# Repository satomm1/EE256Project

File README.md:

# EE 256 Project --- The Smart Pot
Matthew Sato <br />
satomm@stanford.edu <br />
Autumn 2023

This repository contains three folders: [`electrical`](electrical), [`software`](software), and [`docs`](docs) which contain all the project deliverables for this project. The project summary with my perspectives on this project is located at the [bottom of this page](#project-summary).

## The Smart Pot
The smart pot is designed as a completely autonomous plant pot that gives you the ability to be a plant parent without the trouble of remembering to water it on a regular basis. It gives water to the plant when it actually is thirsty. Now you can travel without being worried about watering your plant!

### Features of the Smart Pot
- Senses the ambient air temperature and soil moisture of the plant
- Automatically pumps water into pot when soil moisture drops too low
- Sensor to indicate when the water reservoir is low
- Display to show the temperature
- Ability to change temperature units, activate pump manually, and change the threshold at which the pump is activated
- Serial desktop interface and web-based HTML interface
- The features are fully integrated across the board, serial interface, and webpage. Any update in setting in one of these interfaces results in the corresponding update to the other interfaces.

### Implementation Details of the Smart Pot
- The Smart Pot is built on a PCB and is under the control of a PIC32 microcontroller
- Temperature sensing is performed via a thermistor
- Soil moisture sensing is performed with two probes manufuctured on a PCB
- The water tank sensor is a limit switch which is activated by a plunger when the water is too low
- The WiFi capability is added with an ESP32 and communicates with the PIC32 via SPI
- Powered with a 5 V DC barrel jack
- A 7 segment display implemented with shift registers and SPI
- 2x UART to USB bridges to allow serial communication with a desktop machine

### More Details
To learn more about the product, visit the following folders:
1. [`docs`](docs/): contains the product brief, product requirements, product design document, bill of materials, bringup plan, and unit tests document
2. [`electrical`](electrical/): contains the detailed KiCad schematic and PCB layout
3. [`software`](software/): contains the software for the Smart Pot

### Instruction Manual
The fully functional board appears as follows:

A. The power supply barrel jack. Insert 5V DC only. <br />
B. The display for the product. Can show temperature in F/C, or the soil moisture percentage <br />
C. The function button. Short pressing once will switch the watering frequency to between the low threshold and the high threshold. A long press will activate the pump. A double press activates selection mode. In selection mode, you can click the button to select Fahrenheit units, Celsius Units, or Soil Moisture to display. After 5 seconds of inactivity in selection mode, the display will show the desired quantity.<br />
D. The serial output. Connect this USB-Micro port to your computer and see the current data using a baud rate of 115200. I recommend TeraTerm, and the proper driver for a CP2102 USB-UART driver must be installed on your machine. The output looks like the following:

E. These two LEDs indicate if the low soil moisture threshold or high soil moisture threshold are selected.<br />
F. This blue LED indicates when your water tank is low:

G. The port for the pump<br />
H. The ports for the soil moisture probes. The probes should be placed in the pot approximately one inch apart:

I. The ports for the water tank level sensor. The sensor can be mounted as follows:

The unit should be turned on for approximately 5 minutes before a reliable temperature can be maintained.

All data can also be viewed on a web browser:

# Project Summary
- In retrospect, why you found this project compelling and was the scope of the project comfortable.
    - I liked that this project allowed us to design a product from start to finish. Going through the design process and how this influences the eventual circuit and PCB design was very informative.
    - I thought the scope of the project was fine, just a little more time at the end would have been nice.
- What were the areas that you learned the most.
    - I learned how to design a circuit from start to finish, including choice of parts. Selecting a part from DigiKey can be daunting, but this project helped me learn how to do this.
    - I also learned a lot from the board bringup --- how to test if things are working, and how to fix poorly soldered joints with a heat gun.
- What are you proud of about the project.
    - After taking ME218, I felt confident about my ability to program a microcontroller to do useful tasks. I am proud that I was able to transfer the skills to the PCB using a slightly different microcontroller and now feel like my capabilities are much larger than before.
- What might you do differently.
    - I would have not used any QFN packages in my design --- these are hard to solder!
    - I would have spent more time doing floor planning in the PCB design before routing the copper.
- Now that you know how to build a PCB based system, what might you want to attempt next?
    - I plan to use my PCB knowledge to design PCBs for my research project(s), including the design of a low-level controller for a mobile robot.

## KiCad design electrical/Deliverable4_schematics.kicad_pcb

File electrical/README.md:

# Electrical Design

This folder contains the electrical schematic and PCB layout of the project. The project is available as a KiCad file.

My board produces the soil moisture probes on the PCB. These are cut from the PCB after production via a notcher.

3D View of PCB:

PCB Layout:

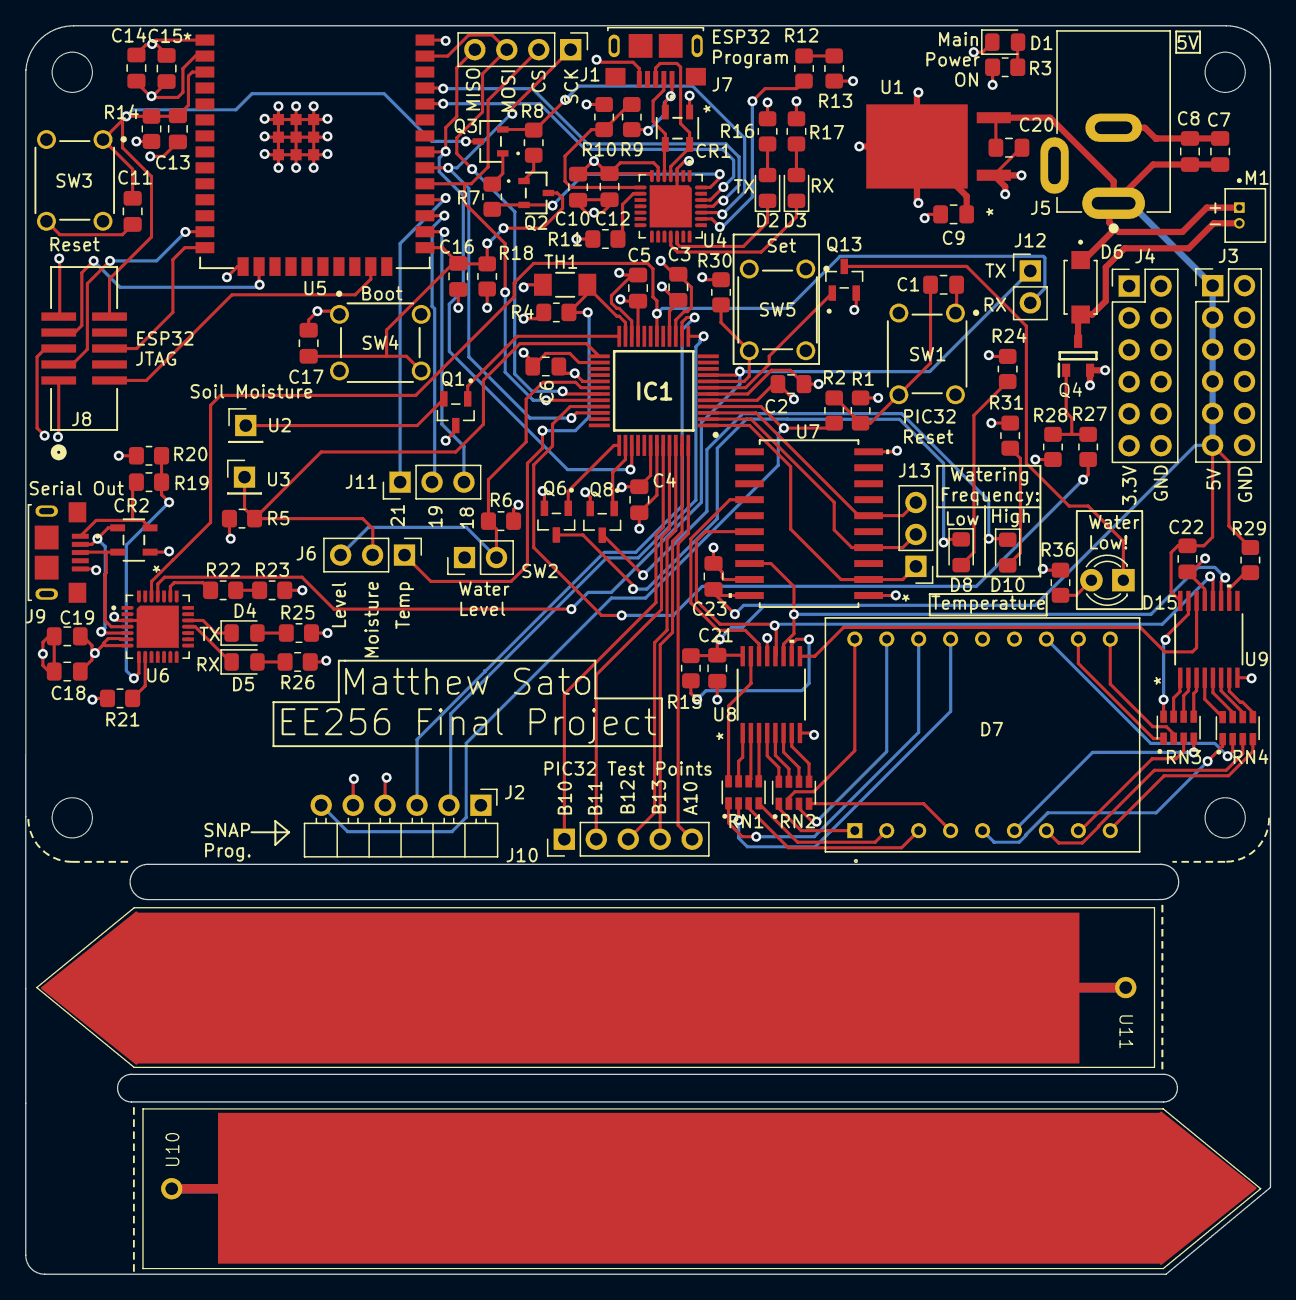
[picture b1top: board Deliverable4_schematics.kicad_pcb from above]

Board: 4 copper layers, 99.0 x 99.3 mm, 114 parts (0 on the bottom side), 117 nets.

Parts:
C1, C2, C3, C4, C5, C6, C7, C10, C11, C13, C15, C16, C17, C18, C21, C22, C23: 0.1 uF; C_0805_2012Metric_Pad1.18x1.45mm_HandSolder
C8, C20: 10 uF; C_0805_2012Metric_Pad1.18x1.45mm_HandSolder
C9, C14: 22 uF; C_0805_2012Metric_Pad1.18x1.45mm_HandSolder
C12, C19: 4.7 uF; C_0805_2012Metric_Pad1.18x1.45mm_HandSolder
CR1, CR2: SP0503BAHTG; TVS-SP05_LTF-M
D1: Main Power On; LED_0805_2012Metric_Pad1.15x1.40mm_HandSolder
D2, D3: LED; LED_0805_2012Metric_Pad1.15x1.40mm_HandSolder
D4: TX Indicator; LED_0805_2012Metric_Pad1.15x1.40mm_HandSolder
D5: RX Indicator; LED_0805_2012Metric_Pad1.15x1.40mm_HandSolder
D6: RS2MAL; SODFL5226X100N
D7: HDSP-523G; LED_HDSP-523G
D8: Set Level 1; LED_0805_2012Metric_Pad1.15x1.40mm_HandSolder
D10: Set Level 2; LED_0805_2012Metric_Pad1.15x1.40mm_HandSolder
D15: Water Level Low; LED_D3.0mm
H1, H2, H3, H4: MountingHole; MountingHole_3.2mm_M3
IC1: PIC32MK0128MCA048-I_Y8X; PIC32MK0128MCA048-I_Y8X__QFP50P900X900X120-48M
J1: SPI1 Test Point; PinHeader_1x04_P2.54mm_Vertical
J2: Programmer; PinHeader_1x06_P2.54mm_Horizontal
J3: 5V Supply Points; PinHeader_2x06_P2.54mm_Vertical
J4: 3.3V Supply Points; PinHeader_2x06_P2.54mm_Vertical
J5: Barrel_Jack; CUI_PJ-002A
J6: Sensor Test Points; PinHeader_1x03_P2.54mm_Vertical
J7, J9: USB_B_Micro; AMPHENOL_10118193-0001LF
J8: 3221-10-0300-00; JTAG__CONN10_3221-10-0300-00_CNC
J10: PIC32 Test Points; PinHeader_1x05_P2.54mm_Vertical
J11: ESP32 Test Points; PinHeader_1x03_P2.54mm_Vertical
J12: UART Test Point; PinHeader_1x02_P2.54mm_Vertical
J13: Shift Register Test Point; PinHeader_1x03_P2.54mm_Vertical
M1: Water Pump; MOLEX_53047-0210
Q1, Q6, Q8, Q13: 2N7002; 2N7002__SOT95P240X111-3N
Q2, Q3: SS8050-G; SS8050-G__TRAN_SS8050-G_CIP-L
Q4: FDN335N; FDN335N__SOT95P251X112-3N
R1, R4, R5, R7, R8, R14, R18: 10k; R_0805_2012Metric_Pad1.20x1.40mm_HandSolder
R2, R6, R11, R12, R15, R21, R22, R29, R30: 1k; R_0805_2012Metric_Pad1.20x1.40mm_HandSolder
R3, R16, R17, R24, R25, R26, R31: 100R; R_0805_2012Metric_Pad1.20x1.40mm_HandSolder
R9, R19: 22.1k; R_0805_2012Metric_Pad1.20x1.40mm_HandSolder
R10, R20: 47.5k; R_0805_2012Metric_Pad1.20x1.40mm_HandSolder
R13, R23: 0R; R_0805_2012Metric_Pad1.20x1.40mm_HandSolder
R27: 220R; R_0805_2012Metric_Pad1.20x1.40mm_HandSolder
R28: 220k; R_0805_2012Metric_Pad1.20x1.40mm_HandSolder
R36: 27R; R_0805_2012Metric_Pad1.20x1.40mm_HandSolder
RN1, RN2, RN3, RN4: CAY16-301J4LF; RESCAF80P320X160X60-8N
SW1, SW3, SW4, SW5: B3F-1020; SW_B3F-1000_OMR
SW2: Water Level; PinHeader_1x02_P2.54mm_Vertical
TH1: 10k @ 25 C; SM_USS-M
U1: AZ1084CD-3.3TRG1; TO-252-3_6P6X6P1_DIO-M
U2, U3: SoilProbe1; PinHeader_1x01_P2.54mm_Vertical
U4, U6: CP2102N-A02-GQFN28R; CP2102-28__IC_CP2102N-A02-GQFN28R
U5: ESP32-WROOM-32E-N8; ESP32­WROOM­32E_EXP
U7: SN74ACT244DWR; DW20-M
U8, U9: SN74HCS595PWR; TSSOP16_PW_TEX-M
U10, U11: SoilMoistureProbe

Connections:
+3.3V: C2.1, C3.2, C4.1, C5.2, C6.1, C9.2, C10.1, C12.1, C14.1, C15.1, C18.1, C19.1, IC1.6 (VDD_1), IC1.15 (AVDD), IC1.22 (VDD_2), IC1.26 (VDD_3), IC1.43 (VDD_4), J2.5, J4.1, J4.3, J4.5, J4.7, J4.9, J4.11, J8.1, Q1.3 (D), R1.1, R3.2, R4.1, R11.1, R14.1, R16.1, R17.1, R18.1, R21.1, R24.2, R25.1, R26.1, R31.2, R36.2, SW2.1, SW5.1, U1.2 (OUTPUT), U4.6 (VDD), U4.7 (VREGIN), U5.2 (3V3), U6.6 (VDD), U6.7 (VREGIN)
+5V: C7.1, C8.1, C20.1, C21.1, C22.1, C23.1, D6.1 (K), J3.1, J3.3, J3.5, J3.7, J3.9, J3.11, J5.1, M1.1 (+), R15.2, R29.2, U1.3 (INPUT), U7.20 (VCC), U8.16 (VCC), U9.16 (VCC)
/Pump/Pump: IC1.33 (AN14_/_RPC10_/_RC10), R27.1
/Sensors/SoilActivate: IC1.24 (TDI_/_FLT15_/_RPB4_/_SCL2_/_RB4), Q1.1 (G)
/Sensors/SoilMoisture: IC1.25 (AN13_/_RPA4_/_T1G_/_RA4), J6.2, R5.1, U3.1
/Sensors/Temp: IC1.23 (DAC1/_AN12_/_RPA8_/_SDA2_/_RA8), J6.1, R4.2, TH1.1
/Sensors/WaterLevel: IC1.30 (RPD8_/_RD8), J6.3, R6.1, SW2.2
/USB_Output/RX_Output: IC1.18 (OA3IN-_/_AN7_/_C3IN1-_/_RPC1_/_RC1), J12.2, U6.26 (TXD)
/USB_Output/TX_Output: IC1.9 (OA2OUT_/_AN0_/_C2IN2-_/_RPA0_/_RA0), J12.1, U6.25 (RXD)
/UserIO/SCK: IC1.1 (RPA7_/_PWML4_/_RA7), J13.1, U7.2 (1A1)
/UserIO/SDO: IC1.3 (RPB15_/_PWML1_/_RB15), J13.3, U7.6 (1A3)
/UserIO/SS: IC1.2 (RPB14_/_PWMH1_/_RB14), J13.2, U7.4 (1A2)
/UserIO/SetLevel1: IC1.37 (TMS_/_AN16_/_LVDIN_/_RPB9_/_RB9), Q6.1 (G)
/UserIO/SetLevel2: IC1.38 (RPC6_/_RC6), Q8.1 (G)
/UserIO/UserButton: IC1.8 (AN10_/_C2IN4-_/_RPA11_/_FLT14_/_RA11), R30.2, SW5.4
/UserIO/WaterLow: IC1.7 (AN11_/_C1IN4-_/_RPA12_/_FLT13_/_RA12), Q13.1 (G)
/WiFi/CS1: IC1.32 (PGC2/RPB6_/_SCL1_/_RB6), J1.2, U5.29 (IO5)
/WiFi/MISO: IC1.39 (RPC7_/_RC7), J1.4, U5.31 (IO19)
/WiFi/MOSI: IC1.31 (PGD2/_RPB5_/_SDA1_/_RB5), J1.3, U5.37 (IO23)
/WiFi/SCK1: IC1.34 (AN15_/_RPB7_/_SCK1_/_INT0_/_RB7), J1.1, U5.30 (IO18)
GND: C1.2, C2.2, C3.1, C4.2, C5.1, C6.2, C7.2, C8.2, C9.1, C10.2, C11.1, C12.2, C13.2, C14.2, C15.2, C16.2, C17.2, C18.2, C19.2, C20.2, C21.2, C22.2, C23.2, CR1.1, CR2.1, D1.1 (K), D7.13, D7.14, IC1.5 (VSS_1), IC1.16 (AVSS), IC1.21 (VSS_2), IC1.29 (VSS_3), IC1.42 (VSS_4), J2.4, J3.2, J3.4, J3.6, J3.8, J3.10, J3.12, J4.2, J4.4, J4.6, J4.8, J4.10, J4.12, J5.2, J7.5 (GND), J8.3, J8.5, J9.5 (GND), Q4.2 (S), Q6.2 (S), Q8.2 (S), Q13.2 (S), R5.2, R6.2, R10.1, R13.2, R20.1, R23.2, R28.2, R30.1, SW1.1, SW3.4, SW4.1, TH1.2, U1.1 (ADJ/GND), U4.3 (GND), U4.29 (EXP), U5.1 (GND), U5.15 (GND), U5.38 (GND), U5.39 (GND), U5.40 (GND), U5.41 (GND), U5.42 (GND), U5.43 (GND), U5.44 (GND), U5.45 (GND), U5.46 (GND), U5.47 (GND), U6.3 (GND), U6.29 (EXP), U7.1 (*1OE), U7.10 (GND), U7.19 (*2OE), U8.8 (GND), U8.13 (*OE), U9.8 (GND), U9.13 (*OE)
unnamed: C1.1, R1.2, R2.1, SW1.4
unnamed: D1.2 (A), R3.1
unnamed: D2.2 (A), R16.2
unnamed: D2.1 (K), U4.19 (GPIO0_TXT)
unnamed: D3.2 (A), R17.2
unnamed: D3.1 (K), U4.18 (GPIO1_RXT)
unnamed: D4.2 (A), R25.2
unnamed: D4.1 (K), U6.19 (GPIO0_TXT)
unnamed: D5.2 (A), R26.2
unnamed: D5.1 (K), U6.18 (GPIO1_RXT)
unnamed: D6.2 (A), M1.2 (-), Q4.3 (D)
unnamed: D7.1, RN2.1
unnamed: D7.2, RN1.4
unnamed: D7.3, RN1.3
unnamed: D7.4, RN2.4
unnamed: D7.5, RN4.1
unnamed: D7.6, RN3.4
unnamed: D7.7, RN4.3
unnamed: D7.8, RN3.3
unnamed: D7.9, RN4.4
unnamed: D7.10, RN3.2
unnamed: D7.11, RN3.1
unnamed: D7.12, RN4.2
unnamed: D7.15, RN1.2
unnamed: D7.16, RN1.1
unnamed: D7.17, RN2.3
unnamed: D7.18, RN2.2
unnamed: D8.2 (A), R24.1
unnamed: D8.1 (K), Q6.3 (D)
unnamed: D10.2 (A), R31.1
unnamed: D10.1 (K), Q8.3 (D)
unnamed: D15.2 (A), R36.1
unnamed: D15.1 (K), Q13.3 (D)
unnamed: IC1.13 (PGC1/OA1IN+_/_AN4_/_C1IN1+_/_C1IN3-_/_R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), J2.2
unnamed: IC1.14 (PGD1/OA1IN-_/_AN5_/_CTCMP_/_C1IN1-_/_RT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), J2.3
unnamed: IC1.48 (PWMH4_/_RA10), J10.5
unnamed: IC1.46 (RPB12_/_PWMH2_/_RB12), J10.3
unnamed: IC1.47 (RPB13_/_PWML2_/_CTPLS_/_RB13), J10.4
unnamed: IC1.45 (TCK_/_RPB11_/_PWML3_/_RB11), J10.2
unnamed: IC1.44 (TDO_/_RPB10_/_PWMH3_/_RB10), J10.1
unnamed: IC1.4 (~MCLR), J2.6, R2.2
unnamed: CR1.4, J7.3 (D+), U4.4 (D+)
unnamed: CR1.3, J7.2 (D-), U4.5 (D-)
unnamed: CR1.2, J7.1 (VBUS), R9.1
unnamed: CR2.4, J9.3 (D+), U6.4 (D+)
unnamed: CR2.3, J9.2 (D-), U6.5 (D-)
unnamed: CR2.2, J9.1 (VBUS), R19.1
unnamed: J11.1, U5.28 (IO17)
unnamed: J11.2, U5.27 (IO16)
unnamed: J11.3, U5.26 (IO4)
unnamed: Q1.2 (S), U2.1
unnamed: Q2.1, R8.2
unnamed: Q3.1, R7.2
unnamed: Q4.1 (G), R27.2, R28.1
unnamed: R12.2, R13.1
unnamed: R22.2, R23.1
unnamed: R12.1, U4.23 (CTS)
unnamed: Q2.2, R7.1, U4.28 (DTR)
unnamed: Q3.2, R8.1, U4.24 (RTS)
unnamed: U4.25 (RXD), U5.35 (TXD0)
unnamed: U4.26 (TXD), U5.34 (RXD0)
unnamed: R9.2, R10.2, U4.8 (VBUS)
unnamed: R11.2, U4.9 (~RST)
unnamed: C11.2, C13.1, J8.10, Q3.3, R14.2, SW3.1, U5.3 (EN)
unnamed: C16.1, C17.1, Q2.3, R18.2, SW4.4, U5.25 (IO0)
unnamed: J8.8, U5.14 (IO12)
unnamed: J8.4, U5.16 (IO13)
unnamed: J8.2, U5.13 (IO14)
unnamed: J8.6, U5.23 (IO15)
unnamed: R22.1, U6.23 (CTS)
unnamed: R19.2, R20.2, U6.8 (VBUS)
unnamed: R21.2, U6.9 (~RST)
unnamed: U7.18 (1Y1), U8.11 (SRCLK), U9.11 (SRCLK)
unnamed: U7.16 (1Y2), U8.12 (RCLK), U9.12 (RCLK)
unnamed: U7.14 (1Y3), U8.14 (SER)
unnamed: R15.1, U8.10 (*SRCLR)
unnamed: RN1.8, U8.15 (QA)
unnamed: RN1.7, U8.1 (QB)
unnamed: RN1.6, U8.2 (QC)
unnamed: RN1.5, U8.3 (QD)
unnamed: RN2.8, U8.4 (QE)
unnamed: RN2.7, U8.5 (QF)
unnamed: RN2.6, U8.6 (QG)
unnamed: U8.9 (QH'), U9.14 (SER)
unnamed: RN2.5, U8.7 (QH)
unnamed: R29.1, U9.10 (*SRCLR)
unnamed: RN3.8, U9.15 (QA)
unnamed: RN3.7, U9.1 (QB)
unnamed: RN3.6, U9.2 (QC)
unnamed: RN3.5, U9.3 (QD)
unnamed: RN4.8, U9.4 (QE)
unnamed: RN4.7, U9.5 (QF)
unnamed: RN4.6, U9.6 (QG)
unnamed: RN4.5, U9.7 (QH)
unnamed: U10.2, U10.3, U10.4
unnamed: U11.2, U11.3, U11.4

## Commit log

2023-12-17 Add project files
